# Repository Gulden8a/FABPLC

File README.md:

# FABPLC
Final project repository

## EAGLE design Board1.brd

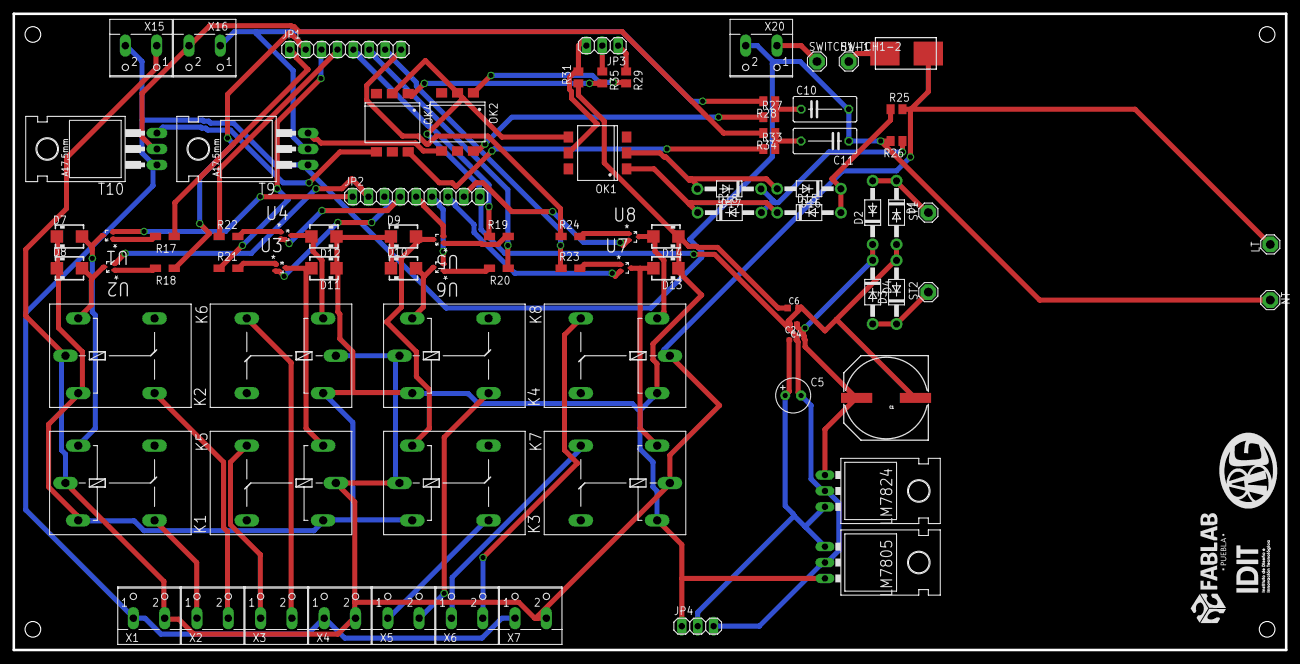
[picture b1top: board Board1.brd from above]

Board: 2 copper layers, 203.2 x 101.6 mm, 84 parts (0 on the bottom side), 66 nets.

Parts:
C1: PANASONIC_H13
C2, C4: 10nF; C0402K
C5: 220uF; E2,5-6
C6: .47uF; C0603K
C10, C11: 100nF; C075-042X103
D1, D2, D3, D4, D15, D16, D17, D18: 1N4004; DO41-10
D7, D8, D9, D10, D11, D12, D13, D14: S1M; SMA
JP1: 1X08
JP2: 1X09
JP3, JP4: 1X03
K1, K2, K3, K4, K5, K6, K7, K8: G5LE
LM7805, LM7824: TO-220-ALT
LT: SE14
NT: SE14
OK1: 4N25SM; DIL6-SMD
OK2, OK4: MOC3021; DIL6-SMD
R17, R18, R19, R20, R21, R22, R23, R24: 1kΩ; R1206W
R25, R26: 30kΩ; M0805
R27, R29, R33, R35: 180Ω; M0805
R28, R34: 2.4kΩ; M0805
R31: 10kΩ; M0805
ST1, ST2: SE14
SWITCH1-1, SWITCH1-2: SE14
T9, T10: BTA206; TO220AB
U1, U2, U3, U4, U5, U6, U7, U8: BC857BT-7-F; SOT50P175X90-3N
U$1: LILFUSE; LITTLEFUSE
X1, X2, X3, X4, X5, X6, X7, X15, X16, X20: W237-102

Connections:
5V: C6.1, D7.C, D8.C, D9.C, D10.C, D11.C, D12.C, D13.C, D14.C, JP4.1, K1.1, K2.1, K3.1, K4.1, K5.2, K6.2, K7.2, K8.2, LM7805.OUT, R31.1
24V: C4.1, C5.+, JP4.2, LM7805.IN, LM7824.OUT
DO0: JP1.1, R17.1
DO1: JP1.2, R18.1
DO2: JP1.3, R21.1
DO3: JP1.4, R22.1
DO4: JP1.5, R19.1
DO5: JP1.6, R20.1
DO6: JP1.7, R23.1
DO7: JP1.8, R24.1
GND: C1.-, C2.2, C4.2, C5.-, C6.2, D1.A, D3.A, JP2.9, JP4.3, LM7805.GND, LM7824.GND, OK1.4, OK2.2, OK4.2
L: K1.P, K2.P, K3.P, K4.P, K5.P, K6.P, K7.P, K8.P, LT.MP, R25.2, X1.2, X4.2, X7.2, X15.1
LEDO0: JP2.1, U1.2
LEDO1: JP2.2, U2.2
LEDO2: JP2.3, U3.2
LEDO3: JP2.4, U4.2
LEDO4: JP2.5, U5.2
LEDO5: JP2.6, U6.2
LEDO6: JP2.7, U7.2
LEDO7: JP2.8, U8.2
LOAD0: R28.2, T9.2, X16.1
LOAD1: R34.2, T10.2, X16.2
N: C10.2, C11.1, NT.MP, R26.2, T9.1, T10.1, X1.1, X4.1, X7.1, X15.2, X20.2
unnamed: SWITCH1-1.MP, X20.1
unnamed: D3.C, D4.A, ST2.MP
unnamed: D8.A, K2.2, U2.3
unnamed: R18.2, U2.1
unnamed: D11.A, K5.1, U3.3
unnamed: D7.A, K1.2, U1.3
unnamed: D9.A, K3.2, U5.3
unnamed: R17.2, U1.1
unnamed: R19.2, U5.1
unnamed: D10.A, K4.2, U6.3
unnamed: R20.2, U6.1
unnamed: R21.2, U3.1
unnamed: D12.A, K6.1, U4.3
unnamed: R22.2, U4.1
unnamed: D13.A, K7.1, U7.3
unnamed: R23.2, U7.1
unnamed: D14.A, K8.1, U8.3
unnamed: R24.2, U8.1
unnamed: D16.A, OK1.2
unnamed: D15.C, D18.C, OK1.1
unnamed: D15.A, D16.C, R25.1
unnamed: D17.C, D18.A, R26.1
unnamed: OK2.6, R27.1
unnamed: C10.1, R27.2, R28.1
unnamed: OK2.4, T9.3
unnamed: OK2.1, R29.2
unnamed: OK4.6, R33.1
unnamed: R33.2, R34.1
unnamed: OK4.4, T10.3
unnamed: OK4.1, R35.2
unnamed: C1.+, C2.1, D2.C, D4.C, LM7824.IN
unnamed: D1.C, D2.A, ST1.MP
OUT0: K1.S, X2.1
OUT1: K2.S, X2.2
OUT2: K5.S, X3.1
OUT3: K6.S, X3.2
OUT4: K3.S, X5.1
OUT5: K4.S, X5.2
OUT6: K7.S, X6.1
OUT7: K8.S, X6.2
P0: JP3.1, R29.1
P1: JP3.2, R35.1
Z0: JP3.3, OK1.5, R31.2

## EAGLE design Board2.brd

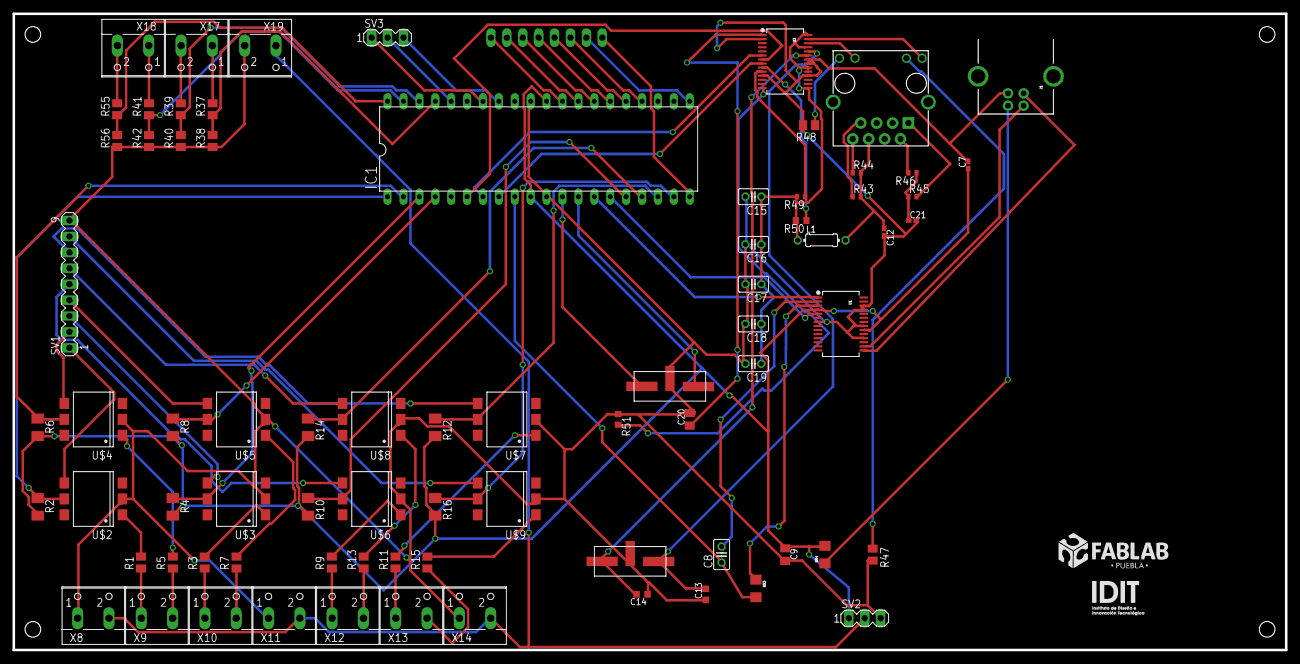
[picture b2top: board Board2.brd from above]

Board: 2 copper layers, 203.2 x 101.6 mm, 78 parts (1 on the bottom side), 79 nets.

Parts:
C7: .1uF; C0402K
C8, C16, C17, C18, C19: 100nF; C025-025X050
C9, C20: 10uF; C0805K
C12, C21: 10nF; C0402K
C13, C14: 10pF; C0603K
C15: C025-025X050
CRYSTAL: 16MHz; SMDCRYSTAL
CRYSTAL2: 25MHz; SMDCRYSTAL
IC1: DIL40
J1: USB-B; USB-B-PTH
J2: MAGJACK
L1: 10uH; 0204/7
R1, R3, R5, R7, R9, R11, R13, R15, R38, R40, R42, R56: 470Ω; M0805
R2, R4, R6, R8, R10, R12, R14, R16: 4.7kΩ; M1206
R37, R39, R41, R55: 1.8kΩ; M0805
R43, R44, R45, R46: 49.9/1%; R0402
R47, R48: 180Ω; M0805
R49: 10kΩ; R0402
R50: 100kΩ; R0603
R51: 2k/1%; R0603
R53: 100; 1206
R54: 0.0; 1206
SV1: MA09-1
SV2, SV3: MA03-1
SV4: MA08-1
U1: FT232RLSSOP; SSOP28DB
U3: SSOP28DB
U$2, U$3, U$4, U$5, U$6, U$7, U$8, U$9: CNY17SMD; DIL6-SMD
X8, X9, X10, X11, X12, X13, X14, X17, X18, X19: W237-102

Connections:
3.3V: C15.1, C16.1, C17.1, C18.1, C19.1, L1.1, R49.2, R50.2, U3.15, U3.19, U3.20, U3.28
5V: C7.1, C9.1, IC1.10, IC1.30, R2.2, R4.2, R6.2, R8.2, R10.2, R12.2, R14.2, R16.2, R54.2, SV2.1, U1.4, U1.20
24V: SV2.2, X8.2, X11.2, X14.2, X19.1
A0: R37.2, X17.1
A1: R39.2, X17.2
A2: R41.2, X18.1
A3: R55.2, X18.2
AA0: IC1.37, R37.1, R38.2
AA1: IC1.38, R39.1, R40.2
AA2: IC1.39, R41.1, R42.2
AA3: IC1.40, R55.1, R56.2
CS: R50.1, U3.9
DI0: IC1.1, R2.1, U$2.5
DI1: IC1.2, R6.1, U$4.5
DI2: IC1.3, R4.1, U$3.5
DI3: IC1.4, R8.1, U$5.5
DI4: IC1.16, R10.1, U$6.5
DI5: IC1.17, R14.1, U$8.5
DI6: IC1.18, R12.1, U$7.5
DI7: IC1.19, R16.1, U$9.5
DO0: IC1.20, SV4.1
DO1: IC1.21, SV4.2
DO2: IC1.24, SV4.3
DO3: IC1.25, SV4.4
DO4: IC1.26, SV4.5
DO5: IC1.27, SV4.6
DO6: IC1.28, SV4.7
DO7: IC1.29, SV4.8
GND: C7.2, C9.2, C12.2, C13.1, C14.1, C15.2, C16.2, C17.2, C18.2, C19.2, C20.2, C21.2, CRYSTAL.GND, CRYSTAL2.GND, IC1.11, IC1.31, J1.GND, R38.1, R40.1, R42.1, R47.2, R48.2, R51.1, R56.1, SV1.9, SV2.3, U1.7, U1.18, U1.21, U1.25, U1.26, U3.11, U3.18, U3.21, U3.22, U$2.2, U$3.2, U$4.2, U$5.2, U$6.2, U$7.2, U$8.2, U$9.2, X8.1, X11.1, X14.1, X19.2
IN0: R1.1, X9.1
IN1: R5.1, X9.2
IN2: R3.1, X10.1
IN3: R7.1, X10.2
IN4: R9.1, X12.1
IN5: R13.1, X12.2
IN6: R11.1, X13.1
IN7: R15.1, X13.2
LEDI0: SV1.1, U$2.4
LEDI1: SV1.2, U$4.4
LEDI2: SV1.3, U$3.4
LEDI3: SV1.4, U$5.4
LEDI4: SV1.5, U$6.4
LEDI5: SV1.6, U$8.4
LEDI6: SV1.7, U$7.4
LEDI7: SV1.8, U$9.4
MISO: IC1.7, U3.6
MOSI: IC1.6, U3.7
unnamed: CRYSTAL.1, IC1.13
unnamed: CRYSTAL.2, IC1.12
unnamed: R1.2, U$2.1
unnamed: R3.2, U$3.1
unnamed: R5.2, U$4.1
unnamed: R7.2, U$5.1
unnamed: R9.2, U$6.1
unnamed: R11.2, U$7.1
unnamed: R13.2, U$8.1
unnamed: R15.2, U$9.1
unnamed: J1.D+, U1.15
unnamed: J2.7, R43.1
unnamed: J2.8, R44.1
unnamed: C12.1, J2.6, L1.2, R43.2, R44.2
unnamed: J2.2, R46.2
unnamed: J2.1, R45.2
unnamed: C13.2, CRYSTAL2.1, U3.24
unnamed: J2.10, R47.1
unnamed: J2.12, R48.1
unnamed: C14.2, CRYSTAL2.2, U3.23
unnamed: C21.1, R45.1, R46.1
unnamed: C8.1, IC1.9, R53.2
unnamed: C20.1, U3.1
unnamed: R51.2, U3.14
unnamed: J1.VBUS, R54.1
P0: IC1.34, SV3.1
P1: IC1.36, SV3.2
RST: R49.1, U3.10
RX0: IC1.15, U1.5
SCK: IC1.8, U3.8
TX0: IC1.14, U1.1
Z0: IC1.33, SV3.3

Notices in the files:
parts and their libraries:
SparkFun-PowerIC: Licensing: Creative Commons ShareAlike 4.0 International - https://creativecommons.org/licenses/by-sa/4.0
